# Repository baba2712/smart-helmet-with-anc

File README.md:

# ANC Safety Helmet

An industrial safety helmet with **hybrid active noise cancellation** (feed-forward + adaptive feedback FxLMS) on an STM32H743. Target: take ~100 dB(A) plant noise down to **≤ 75 dB(A) at the ear** (passive earcup + ANC), below the 85 dB(A) 8-hour limit. Also a built-in **noise dosimeter**, **hear-through** for speech and alarms, a **seal monitor** that measures the cup's attenuation while it is worn and warns when the seal leaks (glasses, hair, a tilted helmet), and an optional **BLE** link.

> Status: **prototype design, not certified PPE.** Nothing has been built or measured on real hardware yet. See [Status](#status).

## Simulated results (100 dB(A) ambient)

| Noise | Open ear | Passive cup | Passive + ANC | Total reduction |
| --- | --- | --- | --- | --- |
| Motor / fan (tonal) | 100.0 | 80.7 | **72.3 dB(A)** | 27.7 dB |
| Compressor | 99.9 | 77.3 | **73.6 dB(A)** | 26.4 dB |
| Broadband (pink) | 99.9 | 72.4 | **69.1 dB(A)** | 30.8 dB |

ANC adds 3–8.5 dB(A) on top of the passive cup; most gain is on tonal machine noise (80–400 Hz). Known limitation: energy below 63 Hz is not reduced. Full report: [`sim/results/summary.md`](sim/results/summary.md).

On **70 real field recordings** (engine, chainsaw, hand saw, helicopter, train, vacuum cleaner, washing machine; ESC-50) the level at the ear ends at 65–75 dB(A): [`sim/results/real_audio.md`](sim/results/real_audio.md). Engine rumble needs ~15 Pa of anti-noise at 63 Hz, which sets a driver requirement (below).

**Seal monitor** (10 noises × 4 seal conditions, one factory baseline): 23/23 leaks that cost ≥ 3 dB flagged in 3–5 s, 0 false alarms: [`sim/results/seal_monitor.md`](sim/results/seal_monitor.md).

## Repository

| Folder | What's in it |
| --- | --- |
| `sim/` | Python plant + noise models, the reference hybrid-FxLMS controller, and the full study (`run_all.py`). Also generates firmware tuning headers. `real_audio.py` runs it on real recordings; `seal_ref.py` / `seal_monitor.py` are the seal monitor's reference and study. |
| `firmware/` | Bare-metal C for STM32H743: 32 kHz ADC→DSP→DAC path, FxLMS core, path identification, dosimeter, hear-through, USB CDC (TinyUSB), BLE UART, flash storage, power/UI. `test/` holds firmware-in-the-loop tests against the sim. |
| `hardware/` | KiCad 7 projects (open fine in KiCad 8/9) for three boards, generated from `hardware/gen/` (Python circuit descriptions → schematic → PCB → Freerouting → fab files). `spice/` verifies the analog chain in ngspice. |
| `mechanical/` | OpenSCAD earcup inserts, driver baffle, outside-mic pod, light pipe / button plunger. Parametric; **measure your earmuff** and edit `params.scad`. `check_fit.py` cross-checks the parts against the PCBs and the cup. |
| `tools/` | `anc_tool.py`: host tool for the USB/BLE command link (status, tuning, calibration, driver test, dose log). `acceptance_test.py`: the per-helmet acceptance / TRL-6 evidence run. |
| `docs/` | Architecture notes; [`bringup_and_test.md`](docs/bringup_and_test.md): order, build, bring-up, calibration and the TRL-6 demonstration. |

## Boards

| Board | Layers | Size | State |
| --- | --- | --- | --- |
| `main-board`: MCU, power, charger, left-ear analog, amp | 4 | 60 × 50 mm, 14 mm corners | Routed; DRC 0 unconnected, 0 electrical errors; fab files in `fab/` |
| `satellite-board`: right-ear mic front ends | 2 | 34 × 26 mm | Routed; DRC 0 errors (silk warnings only); fab files in `fab/` |
| `mic-board`: IM73A135 MEMS mic (×4 per helmet) | 2 | 11 × 13.2 mm | Routed; DRC clean; fab files in `fab/` |

## Build and test

```bash
git clone --recursive <this repo>
pip install -r sim/requirements.txt

python3 sim/run_all.py                 # simulation study + regenerates firmware/inc/anc_tuning.h
python3 sim/real_audio.py --fetch      # ANC on real recordings (downloads ~30 MB of ESC-50 clips)
python3 sim/seal_monitor.py            # seal-monitor study (uses the recordings if present)
cd firmware && make                    # needs arm-none-eabi-gcc; -> build/anc_helmet.bin (~79 KB)
python3 test/test_fil.py               # firmware DSP vs simulation (all pass)

cd .. && python3 hardware/spice/run_spice.py   # analog chain in ngspice
python3 mechanical/check_fit.py                # parts vs PCBs vs cup

cd hardware/gen && python3 build.py sch                           # regenerate schematics
python3 pcb_build.py place main-board && python3 pcb_build.py route main-board
python3 pcb_build.py finish main-board && python3 pcb_build.py tie main-board
python3 pcb_build.py fab main-board
```

`pcb_build.py` needs KiCad 7's Python module (Ubuntu: `apt install kicad kicad-footprints kicad-symbols`, run with the system `python3`) and Freerouting 2.x at `../../tools-dl/freerouting2.jar` (or `FREEROUTING_JAR`).

Verified so far:
- Firmware compiles with `-Werror`: 78.8 KB flash, 38 KB DTCM, 4 KB ITCM.
- Firmware-in-the-loop tests all pass. C matches the Python reference to 0.0 dB(A) on all three noise types, and the output matches to about 1e-4 relative. The seal monitor matches its reference to < 0.001 dB with identical decisions.
- Path identification in a quiet room: 16 dB fit, 0.6% model error.
- Dosimeter: a 94 dB calibrator tone reads 93.99 dB(A); NIOSH dose math checks out.
- SPICE ([`hardware/spice/results/spice_results.md`](hardware/spice/results/spice_results.md)): mic front ends match the simulation's plant, noise ~23 dB(A) SPL; VMID buffer 85–87° phase margin (keep the 10 Ω isolation resistor); DAC reconstruction ~26 µs at 1 kHz.
- Mechanical fit: all checks pass; the main board clears the cup wall by only 0.45 mm (measure your earmuff).

## Status

Done:
- [x] Simulation study and tuned parameters
- [x] Firmware (compiles; DSP verified in the loop against the sim)
- [x] Schematics for all three boards
- [x] Satellite and mic boards routed, with Gerber, BOM and CPL files for JLCPCB
- [x] Real-recording ANC study, SPICE verification of the analog chain, mechanical fit check
- [x] Seal monitor (reference, study, firmware, FIL test)
- [x] Main board fully routed (Freerouting + `hardware/gen/finish_route.py`), fab files for all three boards
- [x] Printable STLs (`mechanical/stl/`, nominal earmuff), driver acceptance test in firmware, acceptance-test runner

Remaining:
- [ ] **Order and build** following [`docs/bringup_and_test.md`](docs/bringup_and_test.md).
- [ ] **Driver:** buy 2-3 candidate 40 mm drivers (16 Ω preferred) and keep one that passes `anc_tool.py driver-test` (≥ 17 Pa/V at 63 Hz in the cup).
- [ ] Open all three boards in KiCad 8/9 for a last ERC/DRC and 3D look before ordering (KiCad 7 DRC here is clean apart from two reviewed connector-courtyard overlaps).
- [ ] Measure the real earmuff, update `mechanical/params.scad`, re-run `check_fit.py`, export STLs.
- [ ] Calibrate and accept each helmet: `python3 tools/acceptance_test.py`, then the TRL-6 run (docs/bringup_and_test.md §6).
- [ ] Bring-up and acoustic test on real hardware: SPL meter plus a 94 dB calibrator.

## Safety

This is a research prototype. It is **not certified hearing protection.** Real PPE needs testing to EN 352 / ANSI S3.19 (or IS 9167 in India). The firmware fails safe: it drops to passive-only on divergence, output clipping, fault or low battery. The passive cup still has to protect on its own.

## License

MIT, © Khaja Baba Shaik.

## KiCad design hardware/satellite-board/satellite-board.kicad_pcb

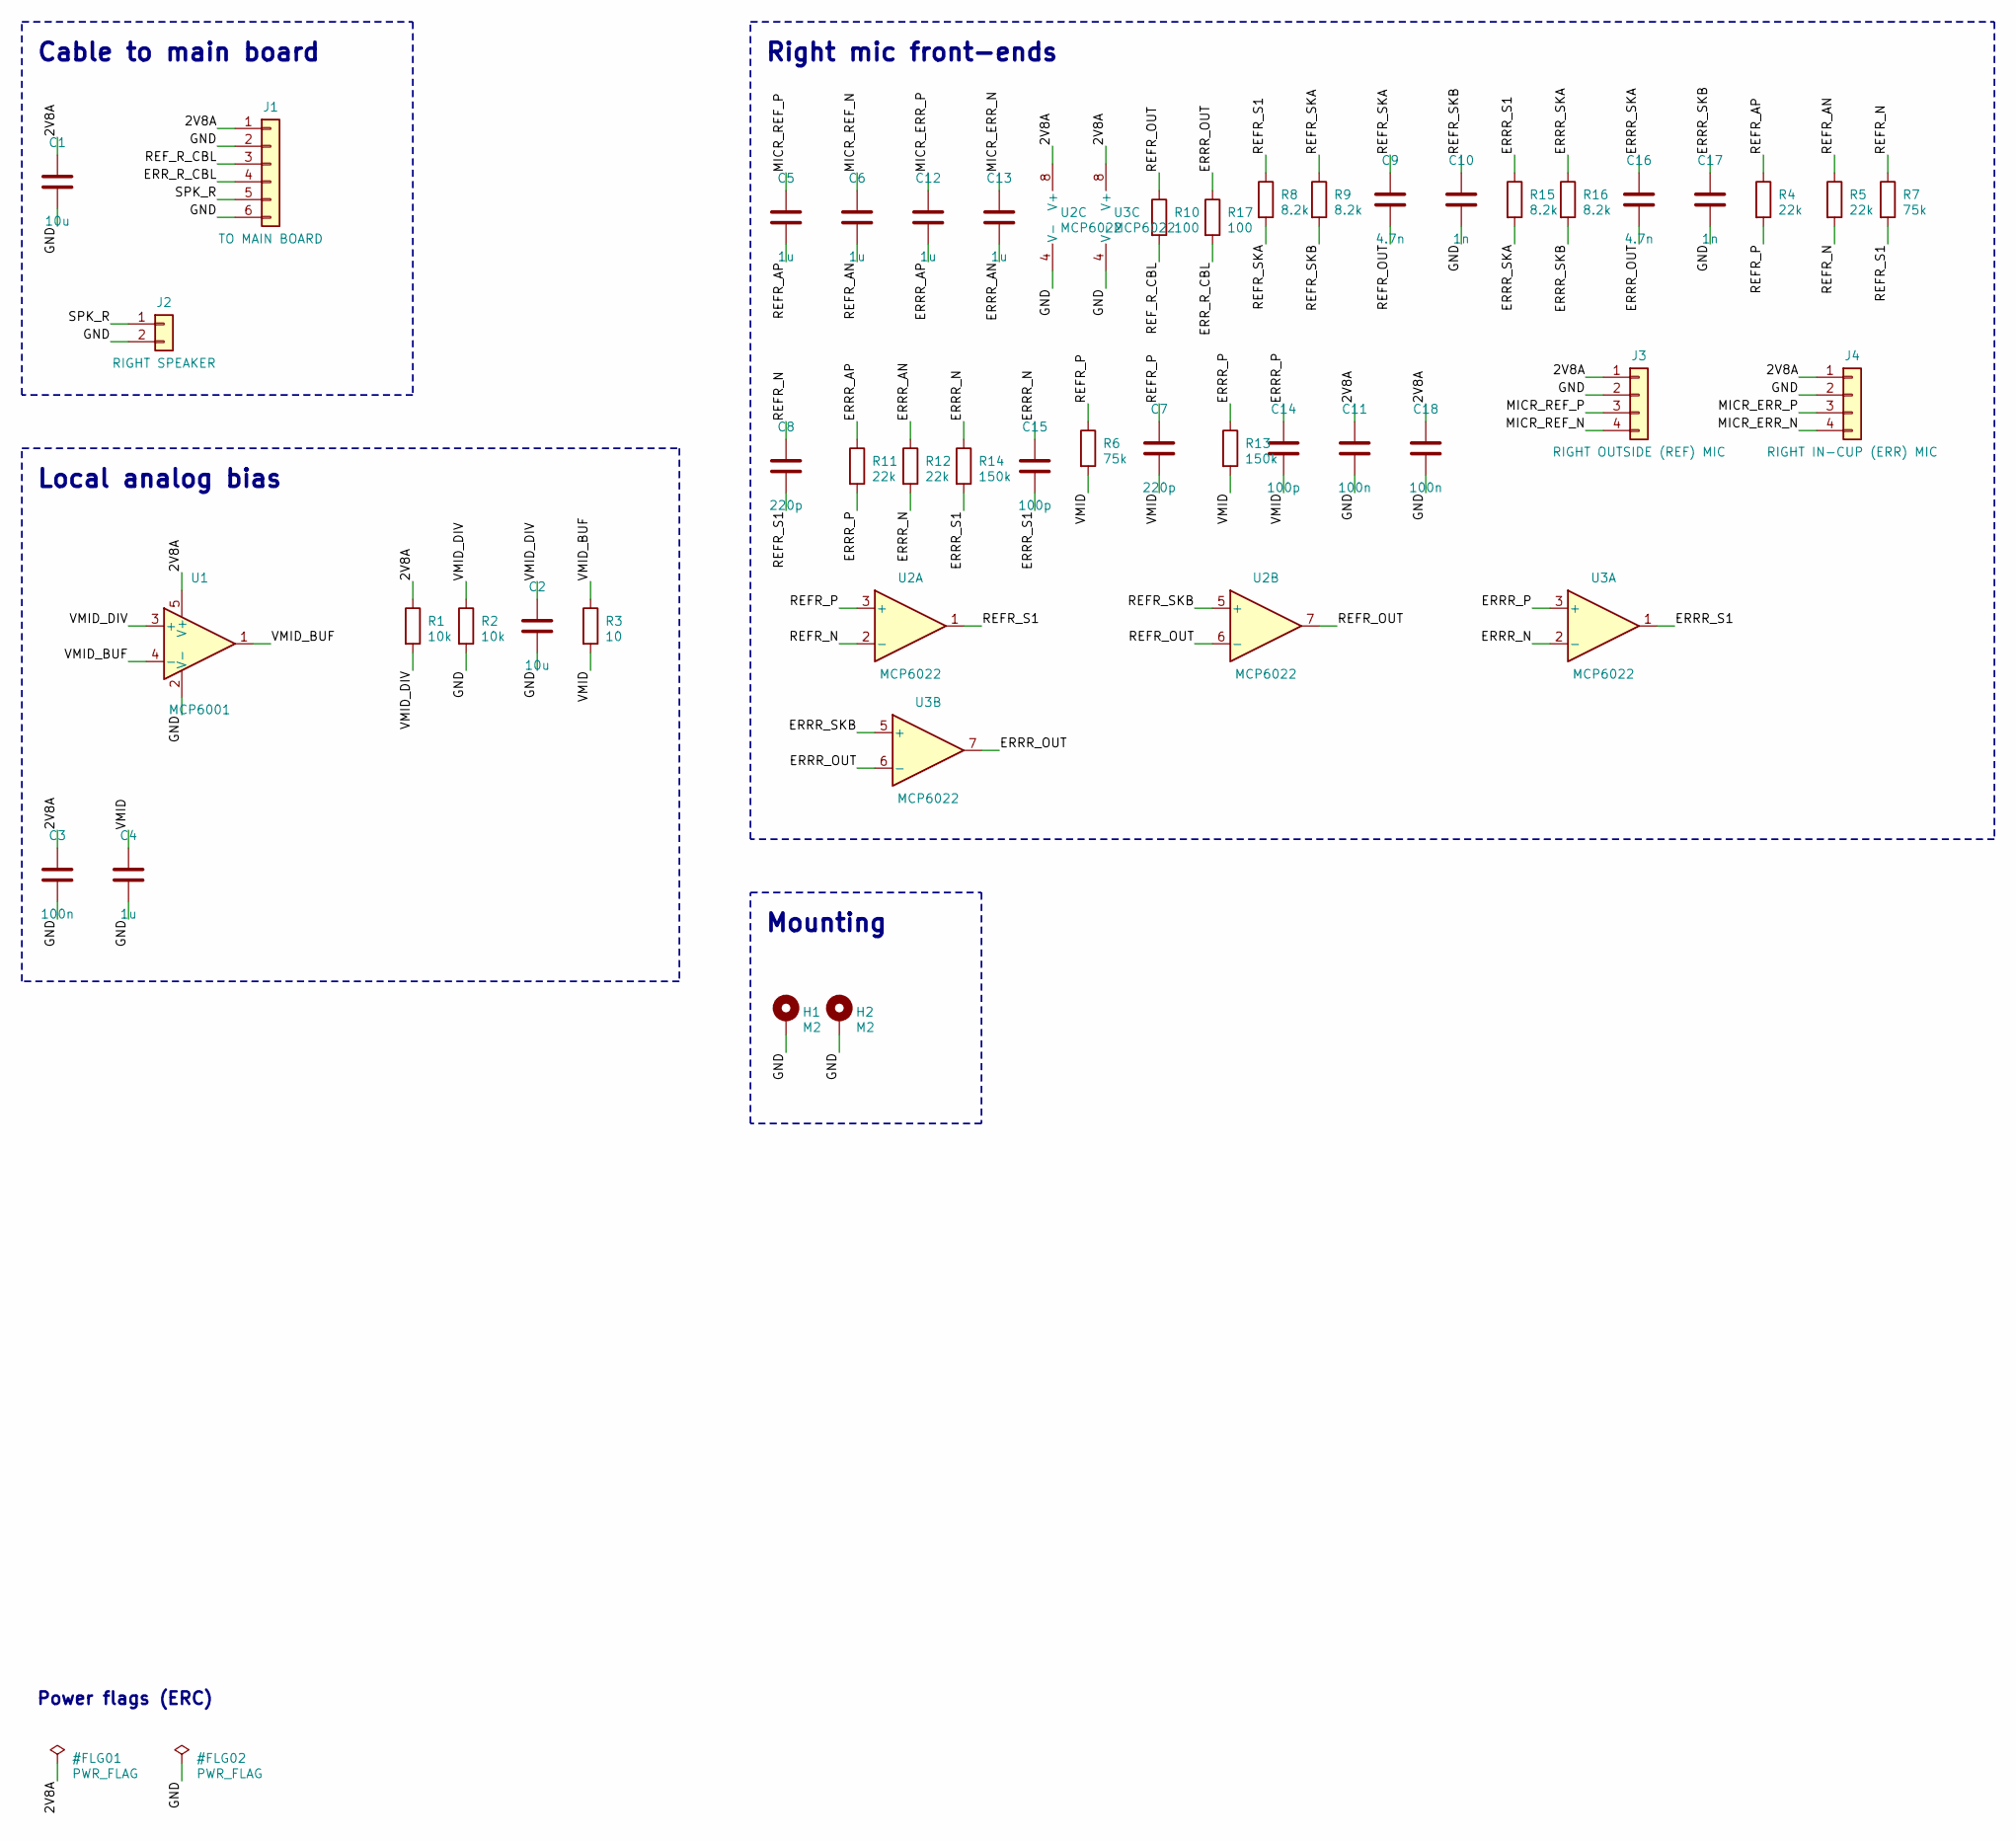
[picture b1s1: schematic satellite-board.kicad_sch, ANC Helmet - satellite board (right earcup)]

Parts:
C1, C2: 10u; C_0805_2012Metric; MPN 10u X5R
C3, C11, C18: 100n; C_0402_1005Metric; MPN 100n X7R
C4, C5, C6, C12, C13: 1u; C_0603_1608Metric; MPN 1u X7R
C7, C8: 220p; C_0402_1005Metric; MPN 220p C0G
C9, C16: 4.7n; C_0603_1608Metric; MPN 4.7n C0G
C10, C17: 1n; C_0402_1005Metric; MPN 1n C0G
C14, C15: 100p; C_0402_1005Metric; MPN 100p C0G
H1, H2: M2; MountingHole_2.2mm_M2_Pad_Via
J1: TO MAIN BOARD; JST_SH_SM06B-SRSS-TB_1x06-1MP_P1.00mm_Horizontal; MPN JST SM06B-SRSS-TB
J2: RIGHT SPEAKER; JST_SH_SM02B-SRSS-TB_1x02-1MP_P1.00mm_Horizontal; MPN JST SM02B-SRSS-TB
J3: RIGHT OUTSIDE (REF) MIC; JST_SH_SM04B-SRSS-TB_1x04-1MP_P1.00mm_Horizontal; MPN JST SM04B-SRSS-TB
J4: RIGHT IN-CUP (ERR) MIC; JST_SH_SM04B-SRSS-TB_1x04-1MP_P1.00mm_Horizontal; MPN JST SM04B-SRSS-TB
R1, R2: 10k; R_0402_1005Metric; MPN 10k 1% 02_1
R3: 10; R_0402_1005Metric; MPN 10 1% 02_1
R4, R5, R11, R12: 22k; R_0402_1005Metric; MPN 22k 1% 02_1
R6, R7: 75k; R_0402_1005Metric; MPN 75k 1% 02_1
R8, R9, R15, R16: 8.2k; R_0402_1005Metric; MPN 8.2k 1% 02_1
R10, R17: 100; R_0402_1005Metric; MPN 100 1% 02_1
R13, R14: 150k; R_0402_1005Metric; MPN 150k 1% 02_1
U1: MCP6001; SOT-23-5; MPN MCP6001T-I/OT
U2, U3: MCP6022; TSSOP-8_4.4x3mm_P0.65mm; MPN MCP6022-I/ST

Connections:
2V8A: C1.1, C3.1, C11.1, C18.1, J1.1, J3.1, J4.1, R1.1, U1.5 (V+), U2.8 (V+), U3.8 (V+)
ERRR_AN: C13.2, R12.1
ERRR_AP: C12.2, R11.1
ERRR_N: C15.1, R12.2, R14.1, U3.2 (-)
ERRR_OUT: C16.2, R17.1, U3.6 (-), U3.7
ERRR_P: C14.1, R11.2, R13.1, U3.3 (+)
ERRR_S1: C15.2, R14.2, R15.1, U3.1
ERRR_SKA: C16.1, R15.2, R16.1
ERRR_SKB: C17.1, R16.2, U3.5 (+)
ERR_R_CBL: J1.4, R17.2
GND: C1.2, C2.2, C3.2, C4.2, C10.2, C11.2, C17.2, C18.2, H1.1, H2.1, J1.2, J1.6, J2.2, J3.2, J4.2, R2.2, U1.2 (V-), U2.4 (V-), U3.4 (V-)
MICR_ERR_N: C13.1, J4.4
MICR_ERR_P: C12.1, J4.3
MICR_REF_N: C6.1, J3.4
MICR_REF_P: C5.1, J3.3
REFR_AN: C6.2, R5.1
REFR_AP: C5.2, R4.1
REFR_N: C8.1, R5.2, R7.1, U2.2 (-)
REFR_OUT: C9.2, R10.1, U2.6 (-), U2.7
REFR_P: C7.1, R4.2, R6.1, U2.3 (+)
REFR_S1: C8.2, R7.2, R8.1, U2.1
REFR_SKA: C9.1, R8.2, R9.1
REFR_SKB: C10.1, R9.2, U2.5 (+)
REF_R_CBL: J1.3, R10.2
SPK_R: J1.5, J2.1
VMID: C4.1, C7.2, C14.2, R3.2, R6.2, R13.2
VMID_BUF: R3.1, U1.1, U1.4 (-)
VMID_DIV: C2.1, R1.2, R2.1, U1.3 (+)

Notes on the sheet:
Cable to main board
Local analog bias
Right mic front-ends
Mounting
Power flags (ERC)

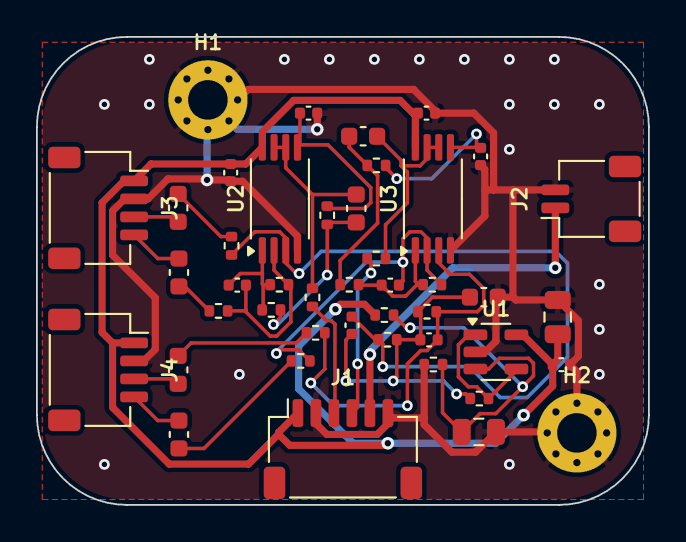
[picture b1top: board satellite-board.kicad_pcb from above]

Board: 2 copper layers, 34.0 x 26.0 mm, 44 parts (0 on the bottom side), 28 nets.

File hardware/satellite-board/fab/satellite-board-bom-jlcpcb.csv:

Comment,Designator,Footprint,Quantity,Manufacturer Part,LCSC Part #,Notes
10u,"C1,C2",C_0805_2012Metric,2,10u X5R,,
1n,"C10,C17",C_0402_1005Metric,2,1n C0G,,
100p,"C14,C15",C_0402_1005Metric,2,100p C0G,,
100n,"C3,C11,C18",C_0402_1005Metric,3,100n X7R,,
1u,"C4,C5,C6,C12,C13",C_0603_1608Metric,5,1u X7R,,
220p,"C7,C8",C_0402_1005Metric,2,220p C0G,,
4.7n,"C9,C16",C_0603_1608Metric,2,4.7n C0G,,
TO MAIN BOARD,J1,JST_SH_SM06B-SRSS-TB_1x06-1MP_P1.00mm_Horizontal,1,JST SM06B-SRSS-TB,,
RIGHT SPEAKER,J2,JST_SH_SM02B-SRSS-TB_1x02-1MP_P1.00mm_Horizontal,1,JST SM02B-SRSS-TB,,
RIGHT OUTSIDE (REF) MIC,J3,JST_SH_SM04B-SRSS-TB_1x04-1MP_P1.00mm_Horizontal,1,JST SM04B-SRSS-TB,,
RIGHT IN-CUP (ERR) MIC,J4,JST_SH_SM04B-SRSS-TB_1x04-1MP_P1.00mm_Horizontal,1,JST SM04B-SRSS-TB,,
10k,"R1,R2",R_0402_1005Metric,2,10k 1% 02_1,,
100,"R10,R17",R_0402_1005Metric,2,100 1% 02_1,,isolates the cable capacitance
150k,"R13,R14",R_0402_1005Metric,2,150k 1% 02_1,,
10,R3,R_0402_1005Metric,1,10 1% 02_1,,
22k,"R4,R5,R11,R12",R_0402_1005Metric,4,22k 1% 02_1,,
75k,"R6,R7",R_0402_1005Metric,2,75k 1% 02_1,,
8.2k,"R8,R9,R15,R16",R_0402_1005Metric,4,8.2k 1% 02_1,,
MCP6001,U1,SOT-23-5,1,MCP6001T-I/OT,,
MCP6022,"U2,U3",TSSOP-8_4.4x3mm_P0.65mm,2,MCP6022-I/ST,,

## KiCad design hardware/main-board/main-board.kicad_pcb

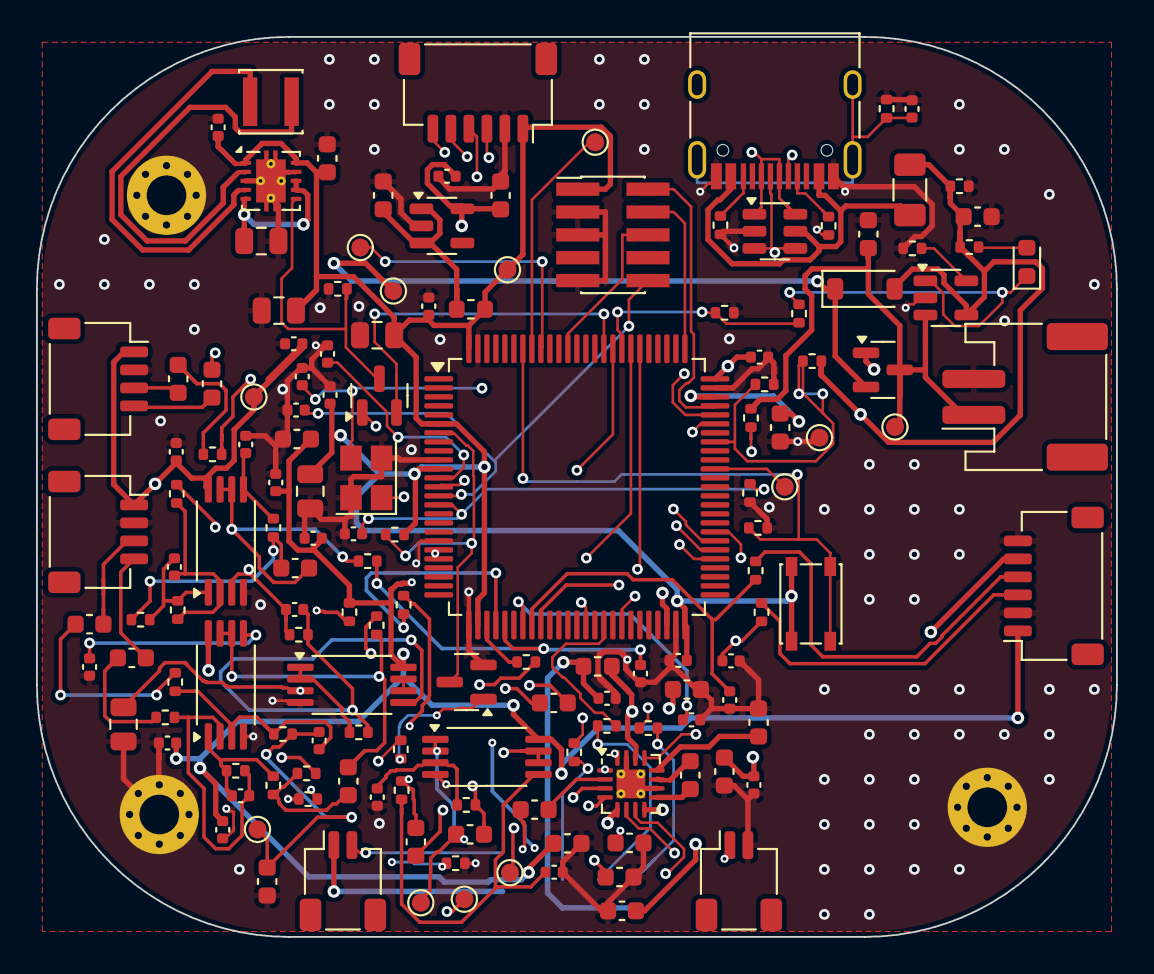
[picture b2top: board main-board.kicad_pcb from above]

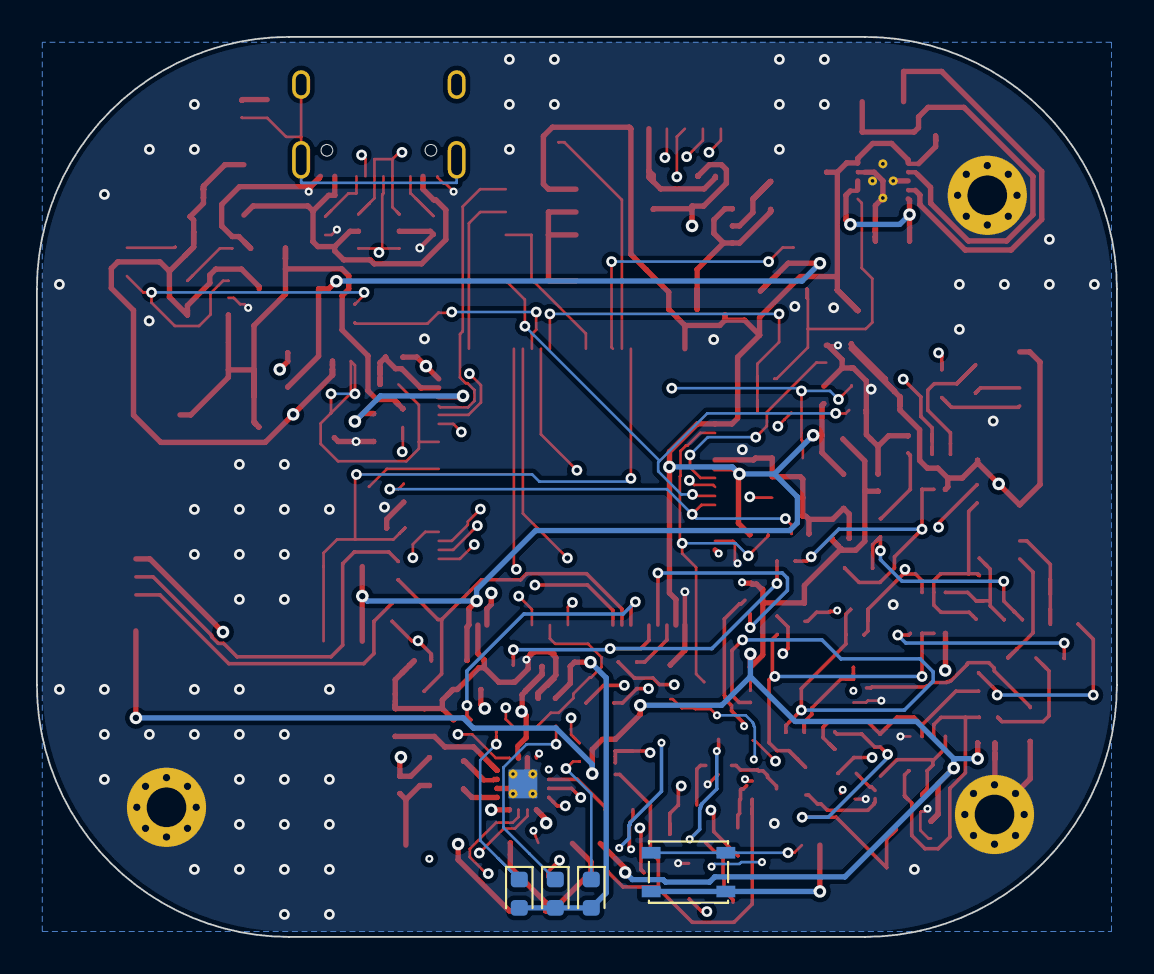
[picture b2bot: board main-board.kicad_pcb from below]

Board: 4 copper layers, 60.0 x 50.0 mm, 154 parts (4 on the bottom side), 99 nets.

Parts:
C1: 4.7n; C_0402_1005Metric
C2, C3, C9, C16: 4.7u; C_0603_1608Metric
C4, C10, C11, C12, C13, C14, C15, C17, C21, C23, C24, C28, C36, C44, C56, C58: 100n; C_0402_1005Metric
C5, C27, C62: 10u; C_0805_2012Metric
C6, C7: 22u; C_0805_2012Metric
C8, C20, C22, C29, C30, C31, C38, C39, C50, C51, C54, C55, C61: 1u; C_0603_1608Metric
C18, C19, C57, C59, C60: 2.2u; C_0603_1608Metric
C25, C26: 12p; C_0402_1005Metric
C32, C33: 220p; C_0402_1005Metric
C34, C42: 4.7n; C_0603_1608Metric
C35, C43: 1n; C_0402_1005Metric
C37, C45, C46, C47: 2.2n; C_0402_1005Metric
C40, C41: 100p; C_0402_1005Metric
C48, C52: 3.3n; C_0603_1608Metric
C49, C53: 1.5n; C_0402_1005Metric
D1: orange; LED_0603_1608Metric
D2: B5819W; D_SOD-123
D3: BAT54C; SOT-23
D4: red; LED_0603_1608Metric
D5: green; LED_0603_1608Metric
D6: blue; LED_0603_1608Metric
F1: 0.5A; Fuse_1206_3216Metric
FB1, FB2: 220R@100MHz; L_0603_1608Metric
H1, H2, H3: M2; MountingHole_2.2mm_M2_Pad_Via
J1: USB-C; USB_C_Receptacle_HRO_TYPE-C-31-M-12
J2: BATTERY 1S Li-ion (protected); JST_PH_S2B-PH-SM4-TB_1x02-1MP_P2.00mm_Horizontal
J3: EXT BUTTON; JST_SH_SM02B-SRSS-TB_1x02-1MP_P1.00mm_Horizontal
J4: SWD; PinHeader_2x05_P1.27mm_Vertical_SMD
J5: LEFT OUTSIDE (REF) MIC; JST_SH_SM04B-SRSS-TB_1x04-1MP_P1.00mm_Horizontal
J6: LEFT IN-CUP (ERR) MIC; JST_SH_SM04B-SRSS-TB_1x04-1MP_P1.00mm_Horizontal
J7: TO RIGHT CUP; JST_SH_SM06B-SRSS-TB_1x06-1MP_P1.00mm_Horizontal
J8: LEFT SPEAKER; JST_SH_SM02B-SRSS-TB_1x02-1MP_P1.00mm_Horizontal
J9: BLE UART MODULE; JST_SH_SM06B-SRSS-TB_1x06-1MP_P1.00mm_Horizontal
L1: 2.2u; L_Changjiang_FNR3015S
Q1: AO3401A; SOT-23
Q2: MMBT3904; SOT-23
R1, R2: 5.1k; R_0402_1005Metric
R3: 1M; R_0402_1005Metric
R4, R9, R10, R11, R12, R13, R15: 100k; R_0402_1005Metric
R5: 200k; R_0402_1005Metric
R6: 2.0k; R_0402_1005Metric
R7, R18, R19: 1k; R_0402_1005Metric
R8, R14: 47k; R_0402_1005Metric
R16, R17, R21, R22: 10k; R_0402_1005Metric
R20: 470; R_0402_1005Metric
R23: 10; R_0402_1005Metric
R24, R25, R31, R32: 22k; R_0402_1005Metric
R26, R27: 75k; R_0402_1005Metric
R28, R29, R35, R36, R40, R41, R42, R43: 8.2k; R_0402_1005Metric
R30, R37, R38, R39: 47; R_0402_1005Metric
R33, R34: 150k; R_0402_1005Metric
SW1: POWER; SW_SPST_PTS810
SW2: BOOT; SW_SPST_PTS810
TP1: 3V3; TestPoint_Pad_D1.0mm
TP2: 2V8A; TestPoint_Pad_D1.0mm
TP3: VSYS; TestPoint_Pad_D1.0mm
TP4: VBAT; TestPoint_Pad_D1.0mm
TP5: VMID; TestPoint_Pad_D1.0mm
TP6: GND; TestPoint_Pad_D1.0mm
TP7: DBG_TP; TestPoint_Pad_D1.0mm
TP8: REF_L; TestPoint_Pad_D1.0mm
TP9: ERR_L; TestPoint_Pad_D1.0mm
TP10: DACL_OUT; TestPoint_Pad_D1.0mm
TP11: I2C1_SCL; TestPoint_Pad_D1.0mm
TP12: I2C1_SDA; TestPoint_Pad_D1.0mm
U1: USBLC6-2SC6; SOT-23-6
U2: MCP73831-2; SOT-23-5
U3: TPS63001; Texas_DRC0010J_ThermalVias
U4: LP5907-2.8; SOT-23-5
U5: STM32H743VIT6; LQFP-100_14x14mm_P0.5mm
U6, U7, U8, U9: MCP6022; TSSOP-8_4.4x3mm_P0.65mm
U10: TPA6132A2; WQFN-16-1EP_3x3mm_P0.5mm_EP1.6x1.6mm_ThermalVias
Y1: 25MHz; Crystal_SMD_3225-4Pin_3.2x2.5mm

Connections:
2V8A: C9.1, C10.1, C20.1, C21.1, C22.1, C23.1, C28.1, C36.1, C44.1, C56.1, J5.1, J6.1, J7.1, R21.1, TP2.1, U4.5, U5.20, U5.21, U6.8, U7.8, U8.8, U9.8
3V3: C6.1, C7.1, C11.1, C12.1, C13.1, C14.1, C15.1, C16.1, C17.1, C62.1, D4.2, D5.2, D6.2, FB1.1, FB2.1, J4.1, J9.1, R16.2, SW2.1, TP1.1, U3.1, U3.10, U5.6, U5.11, U5.27, U5.50, U5.75, U5.100
3V3_AMP: C57.1, C58.1, FB2.2, U10.14
3V3_LDO: C8.1, FB1.2, U4.1, U4.3
AMP_EN: U5.81, U10.13
AMP_G0: U5.82, U10.6
AMP_G1: U5.84, U10.7
AMP_INLN: C51.1, U10.1
AMP_INLP: C50.2, U10.2
AMP_INRN: C55.1, U10.4
AMP_INRP: C54.2, U10.3
BLE_EN: J9.5, U5.57
BLE_RX: J9.4, U5.56
BLE_STATE: J9.6, U5.58
BLE_TX: J9.3, U5.55
BOOT0: R17.1, SW2.2, U5.94
BTN: Q2.3, R16.1, U5.7
BTN_B: Q2.1, R14.2, R15.1
BTN_HI: D3.1, J3.2, R14.1, SW1.2
CC1: J1.A5, R1.1
CC2: J1.B5, R2.1
CHG_LED_A: D1.2, R7.2
CHG_PROG: R6.1, U2.5
CHG_STAT: R8.2, R9.1, U5.83
CHG_STAT_RAW: D1.1, R8.1, U2.1
CPN: C61.2, U10.9
CPP: C61.1, U10.11
DACL_A: C48.1, R40.2, R41.1
DACL_B: C49.1, R41.2, U9.3
DACL_OUT: C48.2, C50.1, TP10.1, U9.1, U9.2
DACR_A: C52.1, R42.2, R43.1
DACR_B: C53.1, R43.2, U9.5
DACR_OUT: C52.2, C54.1, U9.6, U9.7
DAC_L: R40.1, U5.28
DAC_R: R42.1, U5.29
DBG_TP: TP7.1, U5.65
EN_REG: D3.3, R13.1, U3.6
ERRL_AN: C39.2, R32.1
ERRL_AP: C38.2, R31.1
ERRL_N: C41.1, R32.2, R34.1, U8.2
ERRL_OUT: C42.2, R37.1, U8.6, U8.7
ERRL_P: C40.1, R31.2, R33.1, U8.3
ERRL_S1: C41.2, R34.2, R35.1, U8.1
ERRL_SKA: C42.1, R35.2, R36.1
ERRL_SKB: C43.1, R36.2, U8.5
ERR_L: C45.1, R37.2, TP9.1, U5.32
ERR_R: C47.1, R39.2, U5.33
ERR_R_CBL: J7.4, R39.1
GND: C1.2, C2.2, C3.2, C4.2, C5.2, C6.2, C7.2, C8.2, C9.2, C10.2, C11.2, C12.2, C13.2, C14.2, C15.2, C16.2, C17.2, C18.2, C19.2, C20.2, C21.2, C22.2, C23.2, C24.2, C25.2, C26.2, C27.2, C28.2, C29.2, C35.2, C36.2, C37.2, C43.2, C44.2, C45.2, C46.2, C47.2, C49.2, C51.2, C53.2, C55.2, C56.2, C57.2, C58.2, C59.2, C60.2, C62.2, H1.1, H2.1, H3.1, J1.A1, J1.A12, J1.B1, J1.B12, J2.2, J4.3, J4.5, J4.9, J5.2, J6.2, J7.2, J7.6, J8.2, J9.2, Q2.2, R1.2, R2.2, R3.2, R5.2, R6.2, R9.2, R10.2, R12.2, R13.2, R15.2, R17.2, R22.2, TP6.1, U1.2, U2.2, U3.3, U3.9, U3.11, U4.2, U5.10, U5.19, U5.26, U5.49, U5.74, U5.99, U6.4, U7.4, U8.4, U9.4, U10.10, U10.15, U10.17, Y1.2, Y1.4
HPVDD: C59.1, U10.12
HPVSS: C60.1, U10.8
HSE_IN: C25.1, U5.12, Y1.1
HSE_OUT: C26.1, U5.13, Y1.3
I2C1_SCL: TP11.1, U5.92
I2C1_SDA: TP12.1, U5.93
LED_B: R20.2, U5.43
LED_B_K: D6.1, R20.1
LED_G: R19.2, U5.41
LED_G_K: D5.1, R19.1
LED_R: R18.2, U5.39
LED_R_K: D4.1, R18.1
MICL_ERR_N: C39.1, J6.4
MICL_ERR_P: C38.1, J6.3
MICL_REF_N: C31.1, J5.4
MICL_REF_P: C30.1, J5.3
NRST: C24.1, J4.10, U5.14
PWR_HOLD: D3.2, U5.85
REFL_AN: C31.2, R25.1
REFL_AP: C30.2, R24.1
REFL_N: C33.1, R25.2, R27.1, U7.2
REFL_OUT: C34.2, R30.1, U7.6, U7.7
REFL_P: C32.1, R24.2, R26.1, U7.3
REFL_S1: C33.2, R27.2, R28.1, U7.1
REFL_SKA: C34.1, R28.2, R29.1
REFL_SKB: C35.1, R29.2, U7.5
REF_L: C37.1, R30.2, TP8.1, U5.30
REF_R: C46.1, R38.2, U5.34
REF_R_CBL: J7.3, R38.1
SHIELD: C1.1, J1.S1, R3.1
SPK_L: J8.1, U10.16
SPK_R: J7.5, U10.5
SWCLK: J4.4, U5.76
SWDIO: J4.2, U5.72
SWO: J4.6, U5.89
SW_L1: L1.1, U3.4
SW_L2: L1.2, U3.2
USB_DM: J1.A7, J1.B7, U1.3, U1.4, U5.70
USB_DP: J1.A6, J1.B6, U1.1, U1.6, U5.71
U_SPARE_OUT: U6.6, U6.7
VBAT: C3.1, J2.1, Q1.3, R11.1, TP4.1, U2.3
VBAT_SNS: C4.1, R11.2, R12.1, U5.15
VBUS: F1.1, J1.A4, J1.A9, J1.B4, J1.B9, U1.5
VBUS_F: C2.1, D2.2, F1.2, Q1.1, R4.1, R7.1, R10.1, U2.4
VBUS_SNS: R4.2, R5.1, U5.68
VCAP: C18.1, C19.1, U5.48, U5.73
VMID: C29.1, C32.2, C40.2, R23.2, R26.2, R33.2, TP5.1, U6.5
VMID_BUF: R23.1, U6.1, U6.2
VMID_DIV: C27.1, R21.2, R22.1, U6.3
VSYS: C5.1, D2.1, J3.1, Q1.2, SW1.1, TP3.1, U3.5, U3.7, U3.8

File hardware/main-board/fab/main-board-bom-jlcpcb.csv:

Comment,Designator,Footprint,Quantity,Manufacturer Part,LCSC Part #,Notes
4.7n,C1,C_0402_1005Metric,1,4.7n X7R 50V,,
4.7u,C16,C_0603_1608Metric,1,4.7u X7R,,
2.2u,"C18,C19",C_0603_1608Metric,2,2.2u X7R,,
4.7u,"C2,C3",C_0603_1608Metric,2,4.7u X5R 10V,,
12p,"C25,C26",C_0402_1005Metric,2,12p C0G,,
10u,"C27,C62",C_0805_2012Metric,2,10u X5R,,BLE module bulk
220p,"C32,C33",C_0402_1005Metric,2,220p C0G,,
4.7n,"C34,C42",C_0603_1608Metric,2,4.7n C0G,,
1n,"C35,C43",C_0402_1005Metric,2,1n C0G,,
2.2n,"C37,C45,C46,C47",C_0402_1005Metric,4,2.2n C0G,,
100n,"C4,C10,C11,C12,C13,C14,C15,C17,C21,C23,C24,C28,C36,C44,C56,C58",C_0402_1005Metric,16,100n X7R,,VBAT pin; VDDA; VREF+
100p,"C40,C41",C_0402_1005Metric,2,100p C0G,,
3.3n,"C48,C52",C_0603_1608Metric,2,3.3n C0G,,
1.5n,"C49,C53",C_0402_1005Metric,2,1.5n C0G,,
10u,C5,C_0805_2012Metric,1,10u X5R 10V,,
2.2u,"C57,C59,C60",C_0603_1608Metric,3,2.2u X5R,,
22u,"C6,C7",C_0805_2012Metric,2,22u X5R 10V,,
1u,C61,C_0603_1608Metric,1,1u X5R,,
1u,"C8,C20,C22,C29,C30,C31,C38,C39,C50,C51,C54,C55",C_0603_1608Metric,12,1u X7R,,VDDA; VREF+
4.7u,C9,C_0603_1608Metric,1,4.7u X5R,,
orange,D1,LED_0603_1608Metric,1,0603 orange LED,,
B5819W,D2,D_SOD-123,1,B5819W,,
BAT54C,D3,SOT-23,1,BAT54C,,
red,D4,LED_0603_1608Metric,1,0603 red LED,,"BOTTOM SIDE (hand-solder, or order 2-sided assembly)"
green,D5,LED_0603_1608Metric,1,0603 green LED,,"BOTTOM SIDE (hand-solder, or order 2-sided assembly)"
blue,D6,LED_0603_1608Metric,1,0603 blue LED,,"BOTTOM SIDE (hand-solder, or order 2-sided assembly)"
0.5A,F1,Fuse_1206_3216Metric,1,Littelfuse 1206L050YR,,
220R@100MHz,"FB1,FB2",L_0603_1608Metric,2,BLM18PG221SN1D,,
USB-C,J1,USB_C_Receptacle_HRO_TYPE-C-31-M-12,1,HRO TYPE-C-31-M-12,,
BATTERY 1S Li-ion (protected),J2,JST_PH_S2B-PH-SM4-TB_1x02-1MP_P2.00mm_Horizontal,1,JST S2B-PH-SM4-TB,,pin 1 = BAT+ (check your pack's wiring!)
EXT BUTTON,J3,JST_SH_SM02B-SRSS-TB_1x02-1MP_P1.00mm_Horizontal,1,JST SM02B-SRSS-TB,,optional panel button on the cup
SWD,J4,PinHeader_2x05_P1.27mm_Vertical_SMD,1,Cortex debug 2x5 1.27 mm SMD,,
LEFT OUTSIDE (REF) MIC,J5,JST_SH_SM04B-SRSS-TB_1x04-1MP_P1.00mm_Horizontal,1,JST SM04B-SRSS-TB,,
LEFT IN-CUP (ERR) MIC,J6,JST_SH_SM04B-SRSS-TB_1x04-1MP_P1.00mm_Horizontal,1,JST SM04B-SRSS-TB,,
TO RIGHT CUP,J7,JST_SH_SM06B-SRSS-TB_1x06-1MP_P1.00mm_Horizontal,1,JST SM06B-SRSS-TB,,
LEFT SPEAKER,J8,JST_SH_SM02B-SRSS-TB_1x02-1MP_P1.00mm_Horizontal,1,JST SM02B-SRSS-TB,,
BLE UART MODULE,J9,JST_SH_SM06B-SRSS-TB_1x06-1MP_P1.00mm_Horizontal,1,JST SM06B-SRSS-TB,,
2.2u,L1,L_Changjiang_FNR3015S,1,2.2 uH >=1.5 A shielded 3x3 (e.g. TDK VLS3015ET-2R2M),,
AO3401A,Q1,SOT-23,1,AO3401A,,battery -> system when USB absent
MMBT3904,Q2,SOT-23,1,MMBT3904,,
5.1k,"R1,R2",R_0402_1005Metric,2,5.1k 1% 02_1,,
10k,"R16,R17,R21,R22",R_0402_1005Metric,4,10k 1% 02_1,,
470,R20,R_0402_1005Metric,1,470 1% 02_1,,
10,R23,R_0402_1005Metric,1,10 1% 02_1,,
22k,"R24,R25,R31,R32",R_0402_1005Metric,4,22k 1% 02_1,,
75k,"R26,R27",R_0402_1005Metric,2,75k 1% 02_1,,
8.2k,"R28,R29,R35,R36,R40,R41,R42,R43",R_0402_1005Metric,8,8.2k 1% 02_1,,
1M,R3,R_0402_1005Metric,1,1M 1% 02_1,,
47,"R30,R37,R38,R39",R_0402_1005Metric,4,47 1% 02_1,,
150k,"R33,R34",R_0402_1005Metric,2,150k 1% 02_1,,
100k,"R4,R9,R10,R11,R12,R13,R15",R_0402_1005Metric,7,100k 1% 02_1,,
200k,R5,R_0402_1005Metric,1,200k 1% 02_1,,
2.0k,R6,R_0402_1005Metric,1,2.0k 1% 02_1,,500 mA charge current
1k,"R7,R18,R19",R_0402_1005Metric,3,1k 1% 02_1,,
47k,"R8,R14",R_0402_1005Metric,2,47k 1% 02_1,,
POWER,SW1,SW_SPST_PTS810,1,C&K PTS810 SJM 250 SMTR LFS,,"BOTTOM SIDE (hand-solder, or order 2-sided assembly)"
BOOT,SW2,SW_SPST_PTS810,1,C&K PTS810 SJM 250 SMTR LFS,,hold while powering on -> USB DFU
USBLC6-2SC6,U1,SOT-23-6,1,USBLC6-2SC6,,
TPA6132A2,U10,WQFN-16-1EP_3x3mm_P0.5mm_EP1.6x1.6mm_ThermalVias,1,TPA6132A2RTER,,
MCP73831-2,U2,SOT-23-5,1,MCP73831T-2ACI/OT,,
TPS63001,U3,Texas_DRC0010J_ThermalVias,1,TPS63001DRCR,,PS/SYNC high = forced 1.5 MHz PWM (no PFM bursts in the audio band)
LP5907-2.8,U4,SOT-23-5,1,LP5907MFX-2.8/NOPB,,
STM32H743VIT6,U5,LQFP-100_14x14mm_P0.5mm,1,STM32H743VIT6,,
MCP6022,"U6,U7,U8,U9",TSSOP-8_4.4x3mm_P0.65mm,4,MCP6022-I/ST,,unit B unused (follower)
25MHz,Y1,Crystal_SMD_3225-4Pin_3.2x2.5mm,1,25 MHz 3225 CL=10pF +-20ppm (e.g. Abracon ABM8),,

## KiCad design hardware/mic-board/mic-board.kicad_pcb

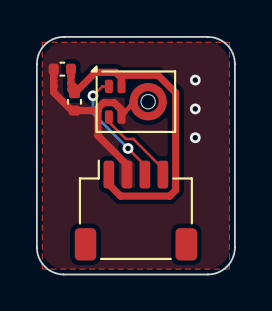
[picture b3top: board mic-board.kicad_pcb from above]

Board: 2 copper layers, 11.0 x 13.2 mm, 4 parts (0 on the bottom side), 4 nets.

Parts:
C1: 100n; C_0402_1005Metric
C2: 1u; C_0402_1005Metric
J1: MIC; JST_SH_SM04B-SRSS-TB_1x04-1MP_P1.00mm_Horizontal
MK1: IM73A135V01; Infineon_PG-LLGA-5-2

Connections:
GND: C1.2, C2.2, J1.2, MK1.4, MK1.5
OUT_N: J1.4, MK1.3
OUT_P: J1.3, MK1.1
VDD: C1.1, C2.1, J1.1, MK1.2

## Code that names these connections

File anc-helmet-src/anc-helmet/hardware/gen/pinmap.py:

"""STM32H743VIT6 (LQFP-100) pin assignment - single source of truth.

Used by the schematic generator (main board nets) and emitted as
firmware/inc/board_pins.h so hardware and firmware can never disagree.
Run:  python3 pinmap.py   (rewrites the header)
"""
import os

# net name -> (port pin, LQFP100 pin number, function / alternate, note)
PINS = {
    # ---- audio: ADC1/ADC2 dual simultaneous, DAC1 ----
    "REF_L":      ("PA6",  30, "ADC12_INP3",  "left outside (reference) mic"),
    "ERR_L":      ("PC4",  32, "ADC12_INP4",  "left inside (error) mic"),
    "REF_R":      ("PB0",  34, "ADC12_INP9",  "right reference mic (via satellite board)"),
    "ERR_R":      ("PC5",  33, "ADC12_INP8",  "right error mic (via satellite board)"),
    "DAC_L":      ("PA4",  28, "DAC1_OUT1",   "left anti-noise out -> recon filter -> amp"),
    "DAC_R":      ("PA5",  29, "DAC1_OUT2",   "right anti-noise out"),
    "VBAT_SNS":   ("PC0",  15, "ADC3_INP10",  "battery / 2"),
    # ---- USB-C (OTG FS) ----
    "USB_DM":     ("PA11", 70, "AF10",        "USB2_OTG_FS DM"),
    "USB_DP":     ("PA12", 71, "AF10",        "USB2_OTG_FS DP"),
    "VBUS_SNS":   ("PA9",  68, "GPIO_IN",     "VBUS * 0.5 (USB present)"),
    # ---- debug ----
    "SWDIO":      ("PA13", 72, "SWD",         ""),
    "SWCLK":      ("PA14", 76, "SWD",         ""),
    "SWO":        ("PB3",  89, "SWO",         ""),
    "DBG_TP":     ("PC8",  65, "GPIO_OUT",    "ISR timing test point"),
    # ---- clocks ----
    "HSE_IN":     ("PH0",  12, "OSC_IN",      "25 MHz crystal"),
    "HSE_OUT":    ("PH1",  13, "OSC_OUT",     ""),
    # ---- UI ----
    "BTN":        ("PC13",  7, "GPIO_IN_PU",  "power/mode button sense via NPN inverter, active low"),
    "LED_R":      ("PE9",  39, "TIM1_CH1",    "RGB LED, common anode, active low"),
    "LED_G":      ("PE11", 41, "TIM1_CH2",    ""),
    "LED_B":      ("PE13", 43, "TIM1_CH3",    ""),
    # ---- power management ----
    "PWR_HOLD":   ("PD4",  85, "GPIO_OUT",    "keeps the buck-boost enabled after the button is released"),
    "CHG_STAT":   ("PD2",  83, "GPIO_IN_PU",  "MCP73831 STAT: low = charging"),
    # ---- headphone amp TPA6132A2 ----
    "AMP_EN":     ("PD0",  81, "GPIO_OUT",    "amp enable (mute when low)"),
    "AMP_G0":     ("PD1",  82, "GPIO_OUT",    "amp gain select bit 0"),
    "AMP_G1":     ("PD3",  84, "GPIO_OUT",    "amp gain select bit 1"),
    # ---- BLE module (optional, UART) ----
    "BLE_TX":     ("PD8",  55, "USART3_TX AF7", "MCU TX -> module RX"),
    "BLE_RX":     ("PD9",  56, "USART3_RX AF7", "module TX -> MCU RX"),
    "BLE_EN":     ("PD10", 57, "GPIO_OUT",    "module enable / reset (high = run)"),
    "BLE_STATE":  ("PD11", 58, "GPIO_IN",     "module 'connected' status"),
    # ---- spare / expansion (test pads) ----
    "I2C1_SCL":   ("PB6",  92, "AF4",         "spare, test pad (fuel gauge option)"),
    "I2C1_SDA":   ("PB7",  93, "AF4",         "spare, test pad"),
}


def header():
    L = ["/* AUTO-GENERATED by hardware/gen/pinmap.py - the schematic uses the same table. */",
         "#ifndef BOARD_PINS_H", "#define BOARD_PINS_H", ""]
    for net, (pin, num, fn, note) in PINS.items():
        port, idx = pin[1], int(pin[2:])
        L.append(f"#define PIN_{net}_PORT  GPIO{port}   /* {pin} (LQFP100 #{num}) {fn}{' - ' + note if note else ''} */")
        L.append(f"#define PIN_{net}_PIN   {idx}u")
    L += ["", "#endif", ""]
    return "\n".join(L)


if __name__ == "__main__":
    out = os.path.join(os.path.dirname(__file__), "..", "..", "firmware", "inc", "board_pins.h")
    with open(out, "w") as fh:
        fh.write(header())
    print("wrote", os.path.normpath(out))
